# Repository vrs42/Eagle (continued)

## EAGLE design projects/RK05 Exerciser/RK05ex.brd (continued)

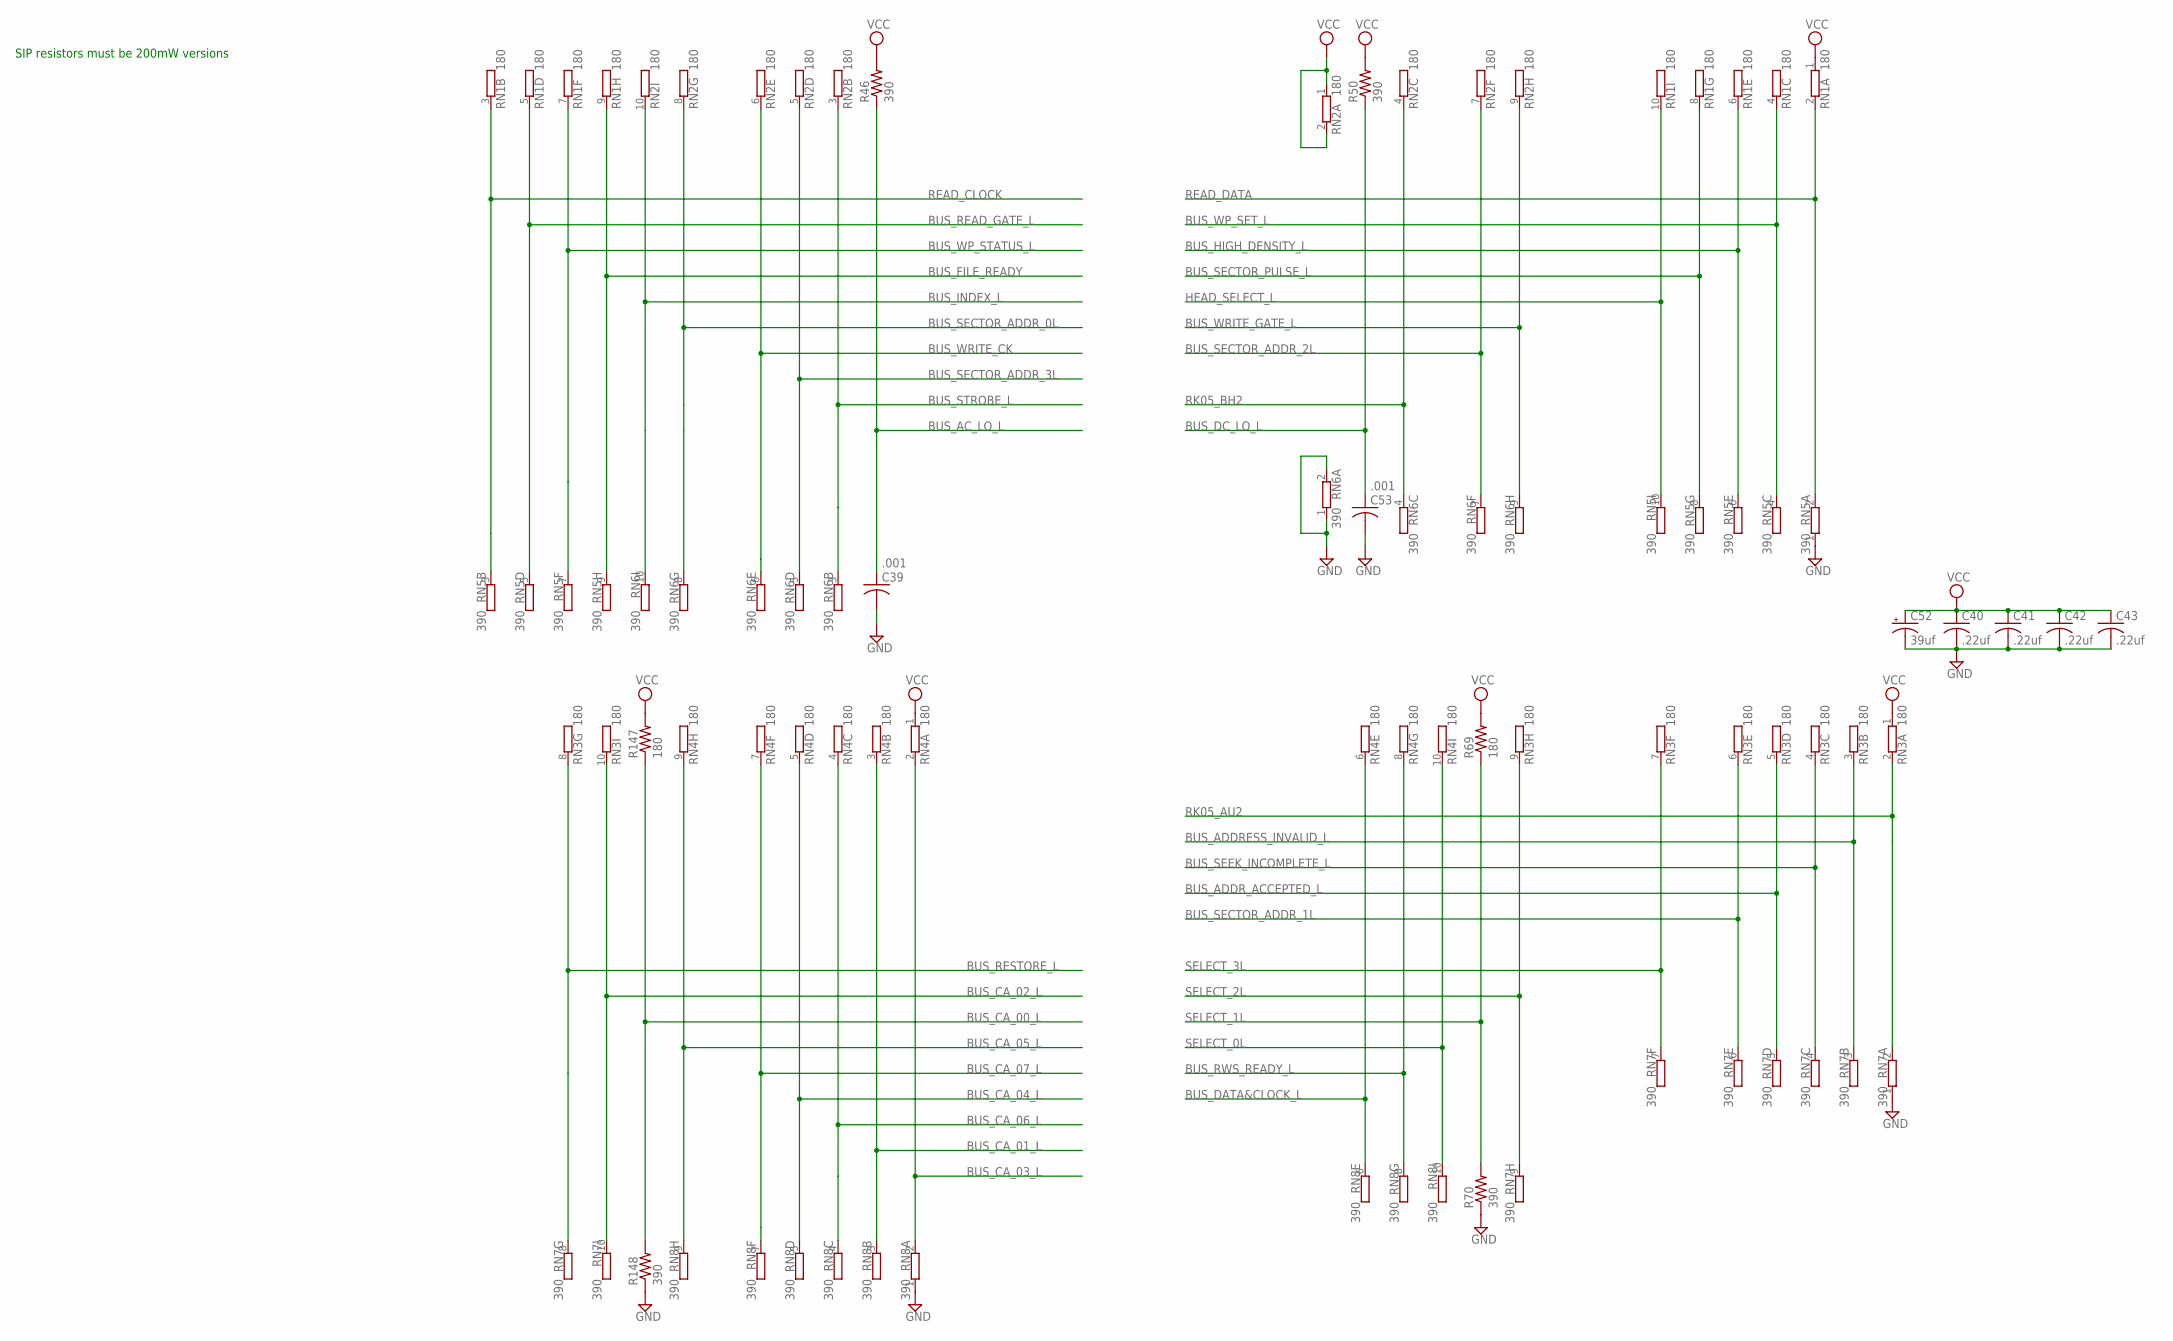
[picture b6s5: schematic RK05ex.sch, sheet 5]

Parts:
C39, C53: .001; C050-025X075
C40, C41, C42, C43: .22uf; C050-025X075
C52: 39uf; E15-5
R46, R50, R70, R148: 390; 0207/10
R69, R147: 180; 0207/10
RN1, RN2, RN3, RN4: 180; SIL10
RN5, RN6, RN7, RN8: 390; SIL10

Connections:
BUS_AC_LO_L: C39.1, R46.1; also elsewhere on the board
BUS_ADDRESS_INVALID_L: RN3.3 (2), RN7.3 (2); also elsewhere on the board
BUS_ADDR_ACCEPTED_L: RN3.5 (2), RN7.5 (2); also elsewhere on the board
BUS_CA_00_L: R147.1, R148.2; also elsewhere on the board
BUS_CA_01_L: RN4.3 (2), RN8.3 (2); also elsewhere on the board
BUS_CA_02_L: RN3.10 (2), RN7.10 (2); also elsewhere on the board
BUS_CA_03_L: RN4.2, RN8.2; also elsewhere on the board
BUS_CA_04_L: RN4.5 (2), RN8.5 (2); also elsewhere on the board
BUS_CA_05_L: RN4.9 (2), RN8.9 (2); also elsewhere on the board
BUS_CA_06_L: RN4.4 (2), RN8.4 (2); also elsewhere on the board
BUS_CA_07_L: RN4.7 (2), RN8.7 (2); also elsewhere on the board
BUS_DATA&CLOCK_L: RN4.6 (2), RN8.6 (2); also elsewhere on the board
BUS_DC_LO_L: C53.1, R50.1; also elsewhere on the board
BUS_FILE_READY: RN1.9 (2), RN5.9 (2); also elsewhere on the board
BUS_HIGH_DENSITY_L: RN1.6 (2), RN5.6 (2); also elsewhere on the board
BUS_INDEX_L: RN2.10 (2), RN6.10 (2); also elsewhere on the board
BUS_READ_GATE_L: RN1.5 (2), RN5.5 (2); also elsewhere on the board
BUS_RESTORE_L: RN3.8 (2), RN7.8 (2); also elsewhere on the board
BUS_RWS_READY_L: RN4.8 (2), RN8.8 (2); also elsewhere on the board
BUS_SECTOR_ADDR_0L: RN2.8 (2), RN6.8 (2); also elsewhere on the board
BUS_SECTOR_ADDR_1L: RN3.6 (2), RN7.6 (2); also elsewhere on the board
BUS_SECTOR_ADDR_2L: RN2.7 (2), RN6.7 (2); also elsewhere on the board
BUS_SECTOR_ADDR_3L: RN2.5 (2), RN6.5 (2); also elsewhere on the board
BUS_SECTOR_PULSE_L: RN1.8 (2), RN5.8 (2); also elsewhere on the board
BUS_SEEK_INCOMPLETE_L: RN3.4 (2), RN7.4 (2); also elsewhere on the board
BUS_STROBE_L: RN2.3 (2), RN6.3 (2); also elsewhere on the board
BUS_WP_SET_L: RN1.4 (2), RN5.4 (2); also elsewhere on the board
BUS_WP_STATUS_L: RN1.7 (2), RN5.7 (2); also elsewhere on the board
BUS_WRITE_CK: RN2.6 (2), RN6.6 (2); also elsewhere on the board
BUS_WRITE_GATE_L: RN2.9 (2), RN6.9 (2); also elsewhere on the board
GND: C39.2, C40.2, C41.2, C42.2, C43.2, C52.-, C53.2, R70.1, R148.1, RN5.1, RN6.1, RN6.2, RN7.1, RN8.1; also elsewhere on the board
HEAD_SELECT_L: RN1.10 (2), RN5.10 (2); also elsewhere on the board
READ_CLOCK: RN1.3 (2), RN5.3 (2); also elsewhere on the board
READ_DATA: RN1.2, RN5.2; also elsewhere on the board
RK05_AU2: RN3.2, RN7.2; also elsewhere on the board
RK05_BH2: RN2.4 (2), RN6.4 (2); also elsewhere on the board
SELECT_0L: RN4.10 (2), RN8.10 (2); also elsewhere on the board
SELECT_1L: R69.1, R70.2; also elsewhere on the board
SELECT_2L: RN3.9 (2), RN7.9 (2); also elsewhere on the board
SELECT_3L: RN3.7 (2), RN7.7 (2); also elsewhere on the board
VCC: C40.1, C41.1, C42.1, C43.1, C52.+, R46.2, R50.2, R69.2, R147.2, RN1.1, RN2.1, RN2.2, RN3.1, RN4.1; also elsewhere on the board

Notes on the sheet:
SIP resistors must be 200mW versions

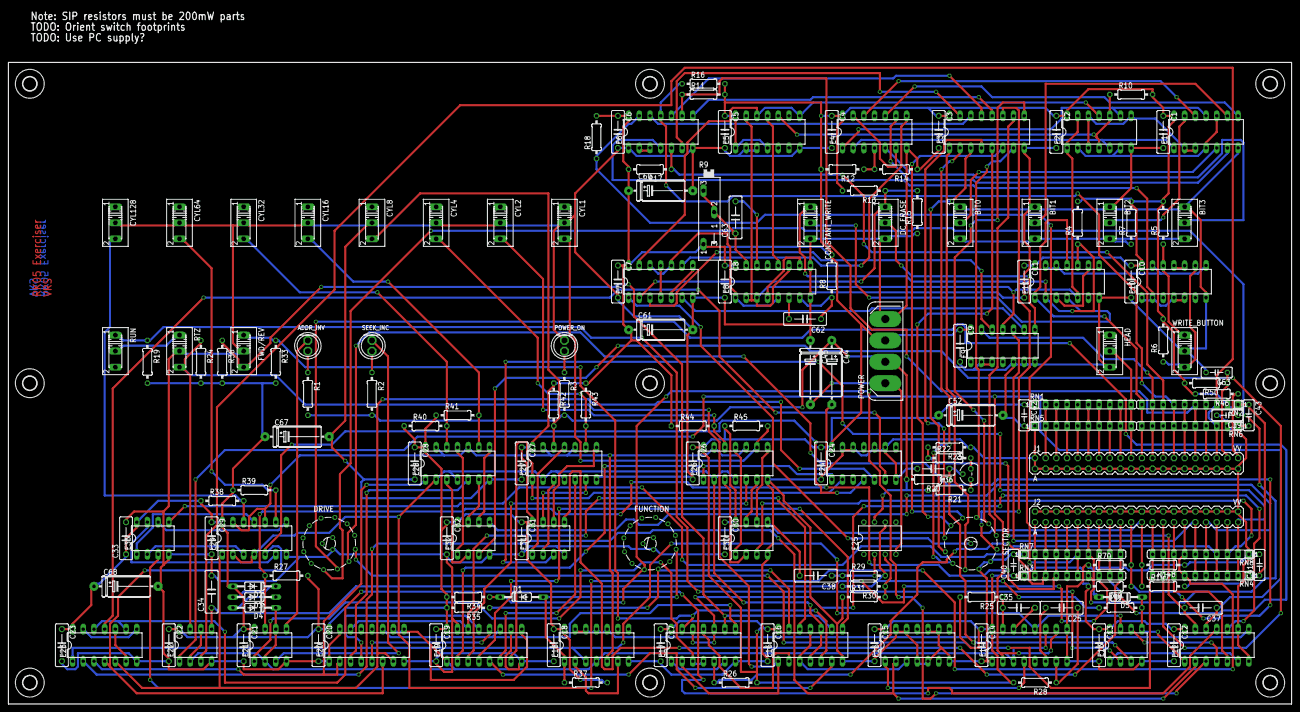
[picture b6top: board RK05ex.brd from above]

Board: 2 copper layers, 304.8 x 152.4 mm, 188 parts (0 on the bottom side), 182 nets.

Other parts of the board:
U$1, U$2, U$3, U$4, U$5, U$6, U$7, U$8, U$9: 3,3
